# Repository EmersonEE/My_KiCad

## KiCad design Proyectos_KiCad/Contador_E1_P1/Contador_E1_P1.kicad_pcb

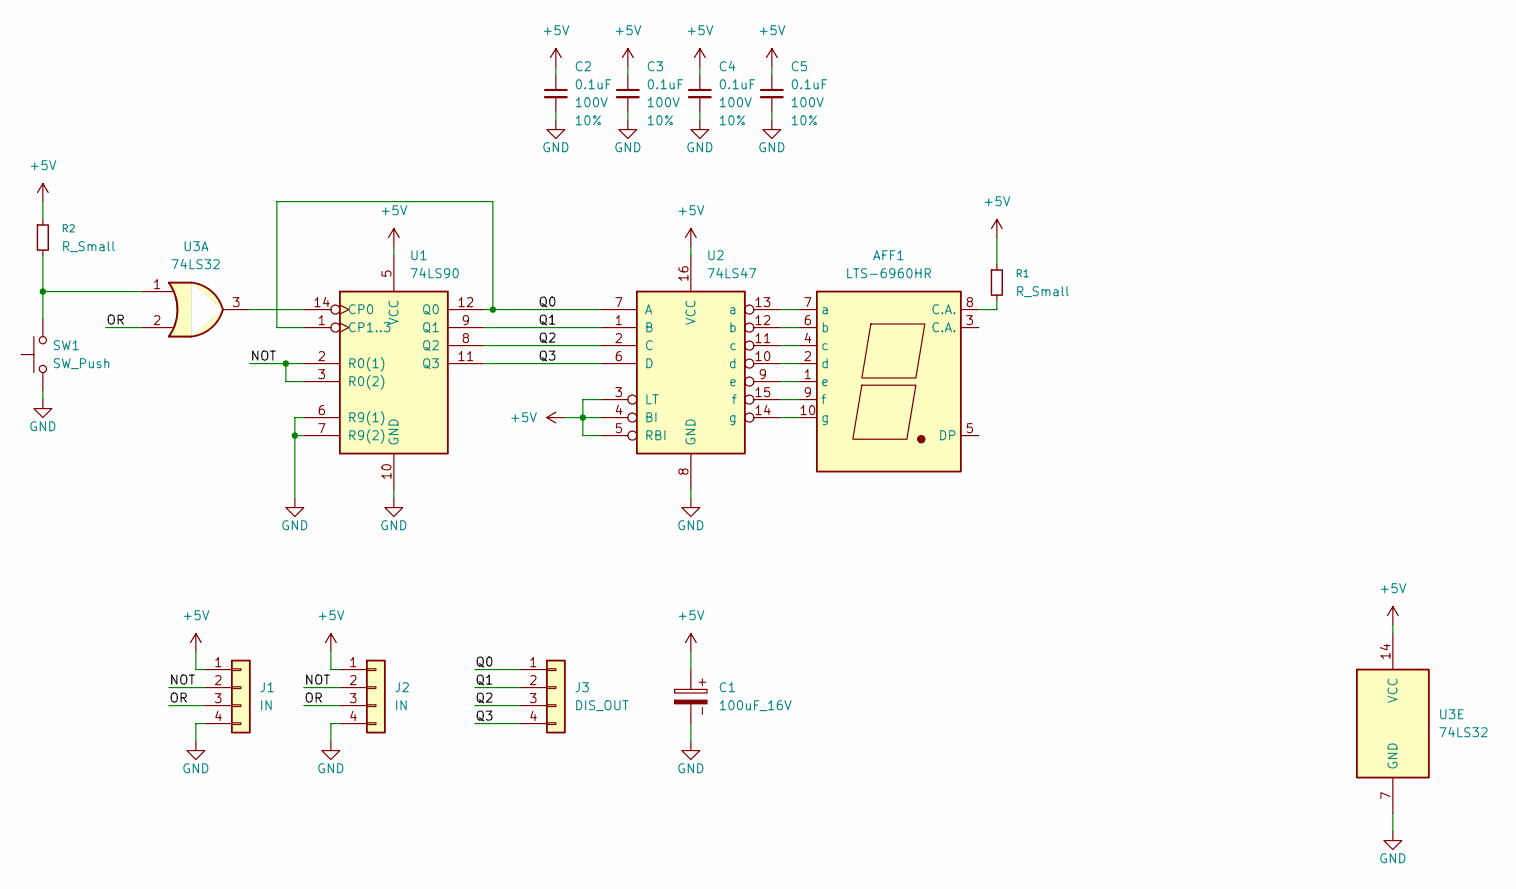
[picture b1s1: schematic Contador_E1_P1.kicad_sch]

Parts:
AFF1: LTS-6960HR; 7SegmentLED_LTS6760_LTS6780
C1: 100uF_16V; CP_Radial_D5.0mm_P2.00mm
C2, C3, C4, C5: 0.1uF; C_0805_2012Metric; Voltage 100V; Tolerance 10%
J1, J2: IN; PinHeader_1x04_P2.54mm_Vertical
J3: DIS_OUT; PinHeader_1x04_P2.54mm_Vertical
R1, R2: R_Small; 1K
SW1: SW_Push; SW_PUSH_6mm
U1: 74LS90; DIP-14_W7.62mm_LongPads
U2: 74LS47; DIP-16_W7.62mm_LongPads
U3: 74LS32; DIP-14_W7.62mm_LongPads

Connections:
+5V: C1.1, C2.1, C3.1, C4.1, C5.1, J1.1, J2.1, R1.1, R2.1, U1.5 (VCC), U2.3 (LT), U2.4 (BI), U2.5 (RBI), U2.16 (VCC), U3.14 (VCC)
/NOT: J1.2, J2.2, U1.2 (R0(1)), U1.3 (R0(2))
/OR: J1.3, J2.3, U3.2
/Q0: J3.1, U1.1 (CP1..3), U1.12 (Q0), U2.7 (A)
/Q1: J3.2, U1.9 (Q1), U2.1 (B)
/Q2: J3.3, U1.8 (Q2), U2.2 (C)
/Q3: J3.4, U1.11 (Q3), U2.6 (D)
GND: C1.2, C2.2, C3.2, C4.2, C5.2, J1.4, J2.4, SW1.1, U1.6 (R9(1)), U1.7 (R9(2)), U1.10 (GND), U2.8 (GND), U3.7 (GND)
unnamed: AFF1.8 (C.A.), R1.2
unnamed: AFF1.7 (a), U2.13 (a)
unnamed: AFF1.6 (b), U2.12 (b)
unnamed: AFF1.4 (c), U2.11 (c)
unnamed: AFF1.2 (d), U2.10 (d)
unnamed: AFF1.1 (e), U2.9 (e)
unnamed: AFF1.9 (f), U2.15 (f)
unnamed: AFF1.10 (g), U2.14 (g)
unnamed: R2.2, SW1.2, U3.1
unnamed: U1.14 (CP0), U3.3

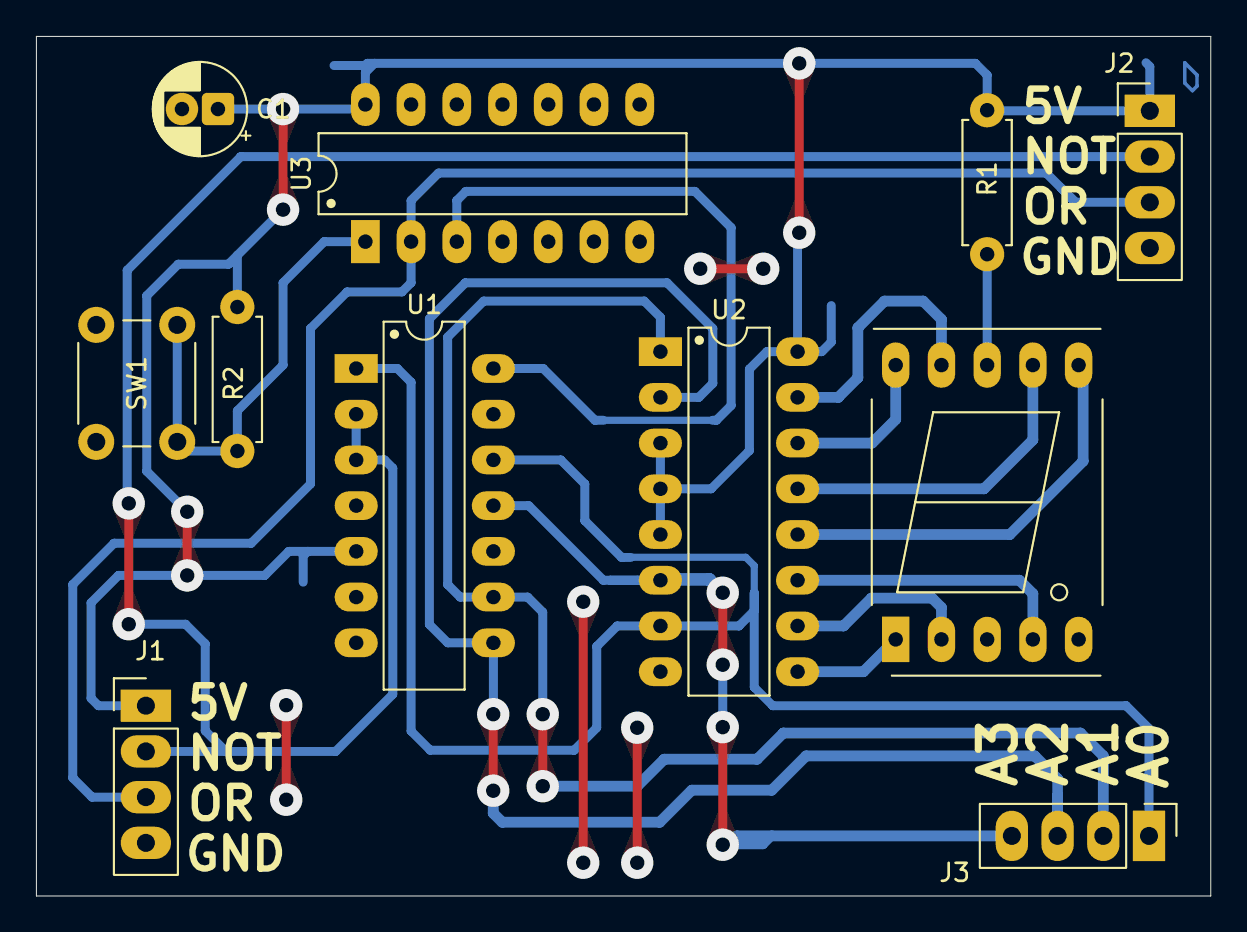
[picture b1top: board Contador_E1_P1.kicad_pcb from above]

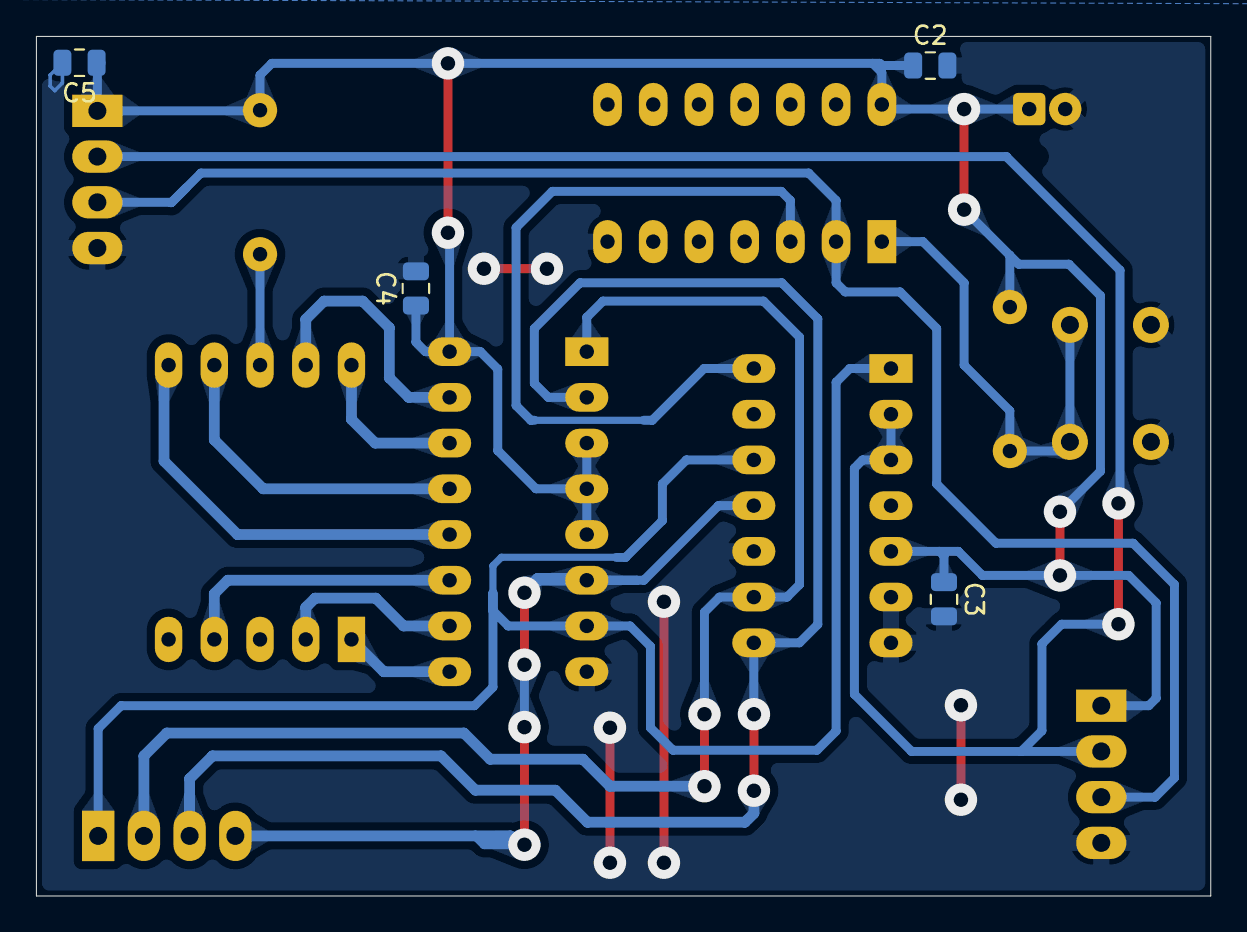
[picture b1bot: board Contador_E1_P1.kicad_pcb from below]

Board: 2 copper layers, 65.2 x 47.8 mm, 15 parts (4 on the bottom side), 18 nets.

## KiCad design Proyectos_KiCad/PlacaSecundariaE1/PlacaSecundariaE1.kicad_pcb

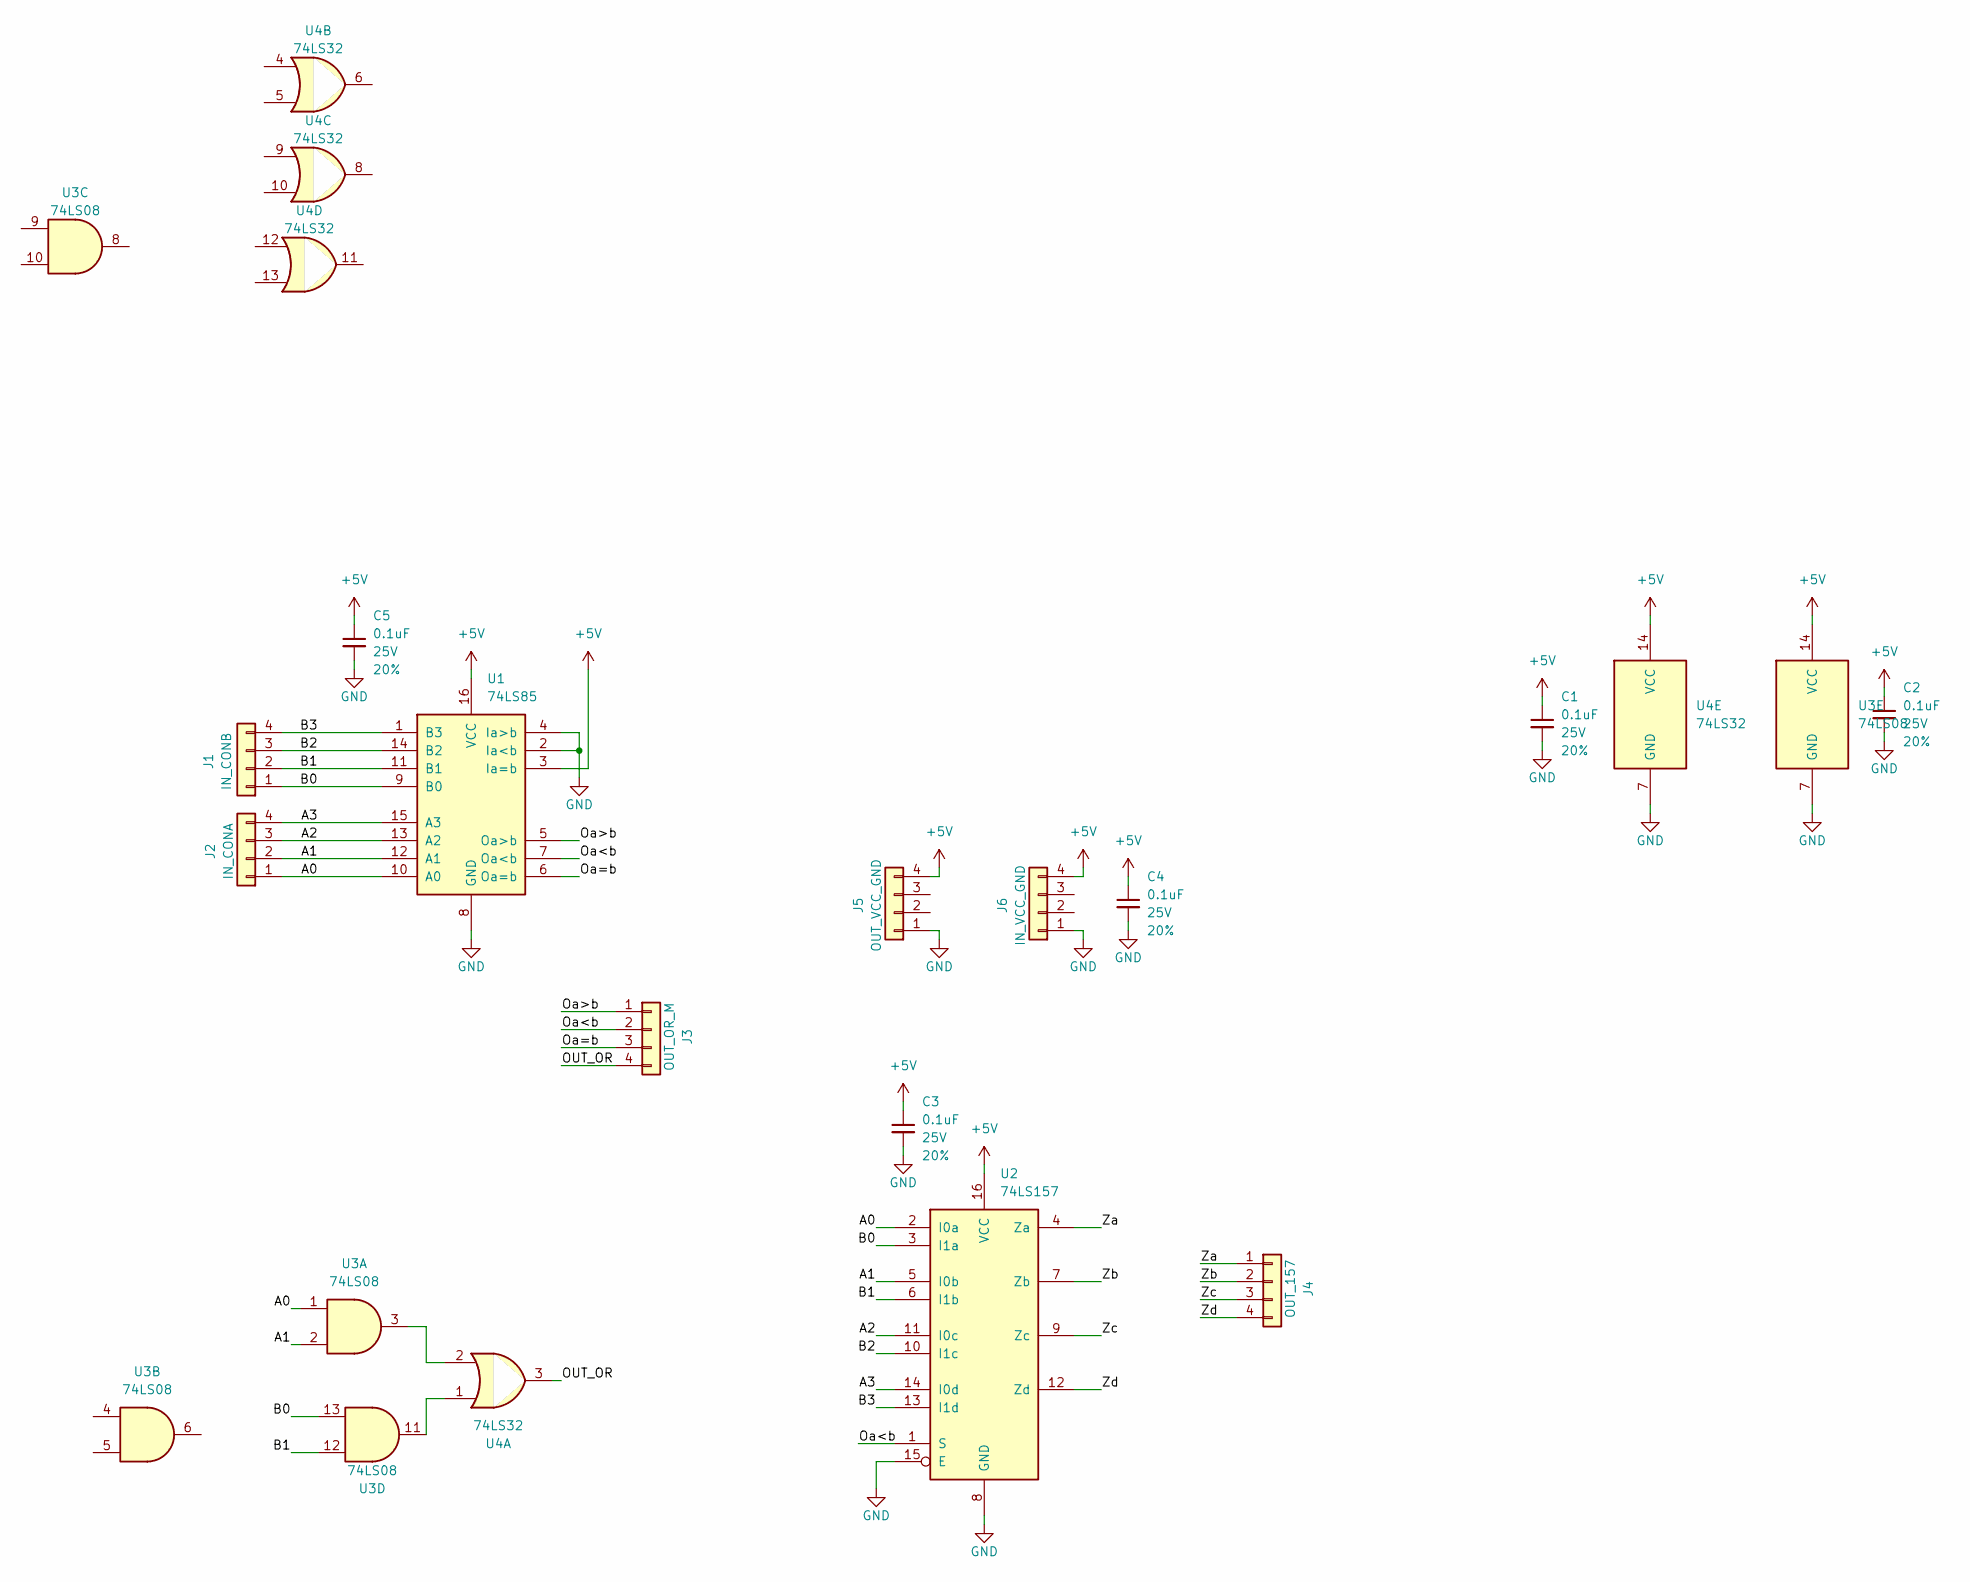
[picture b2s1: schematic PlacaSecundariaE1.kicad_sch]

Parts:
C1, C2, C3, C4, C5: 0.1uF; C_0805_2012Metric; Voltage 25V; Tolerance 20%
J1: IN_CONB; PinHeader_1x04_P2.54mm_Vertical
J2: IN_CONA; PinHeader_1x04_P2.54mm_Vertical
J3: OUT_OR_M; PinHeader_1x04_P2.54mm_Vertical
J4: OUT_157; PinHeader_1x04_P2.54mm_Vertical
J5: OUT_VCC_GND; PinHeader_1x04_P2.54mm_Vertical
J6: IN_VCC_GND; PinHeader_1x04_P2.54mm_Vertical
U1: 74LS85; DIP-16_W7.62mm_LongPads
U2: 74LS157; DIP-16_W7.62mm_LongPads
U3: 74LS08; DIP-14_W7.62mm_LongPads
U4: 74LS32; DIP-14_W7.62mm_LongPads

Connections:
+5V: C1.1, C2.1, C3.1, C4.1, C5.1, J5.4, J6.4, U1.3 (Ia=b), U1.16 (VCC), U2.16 (VCC), U3.14 (VCC), U4.14 (VCC)
/A0: J2.1, U1.10 (A0), U2.2 (I0a), U3.1
/A1: J2.2, U1.12 (A1), U2.5 (I0b), U3.2
/A2: J2.3, U1.13 (A2), U2.11 (I0c)
/A3: J2.4, U1.15 (A3), U2.14 (I0d)
/B0: J1.1, U1.9 (B0), U2.3 (I1a), U3.13
/B1: J1.2, U1.11 (B1), U2.6 (I1b), U3.12
/B2: J1.3, U1.14 (B2), U2.10 (I1c)
/B3: J1.4, U1.1 (B3), U2.13 (I1d)
/OUT_OR: J3.4, U4.3
/Oa<b: J3.2, U1.7 (Oa<b), U2.1 (S)
/Oa=b: J3.3, U1.6 (Oa=b)
/Oa>b: J3.1, U1.5 (Oa>b)
/Za: J4.1, U2.4 (Za)
/Zb: J4.2, U2.7 (Zb)
/Zc: J4.3, U2.9 (Zc)
/Zd: J4.4, U2.12 (Zd)
GND: C1.2, C2.2, C3.2, C4.2, C5.2, J5.1, J6.1, U1.2 (Ia<b), U1.4 (Ia>b), U1.8 (GND), U2.8 (GND), U2.15 (E), U3.7 (GND), U4.7 (GND)
unnamed: U3.3, U4.2
unnamed: U3.11, U4.1

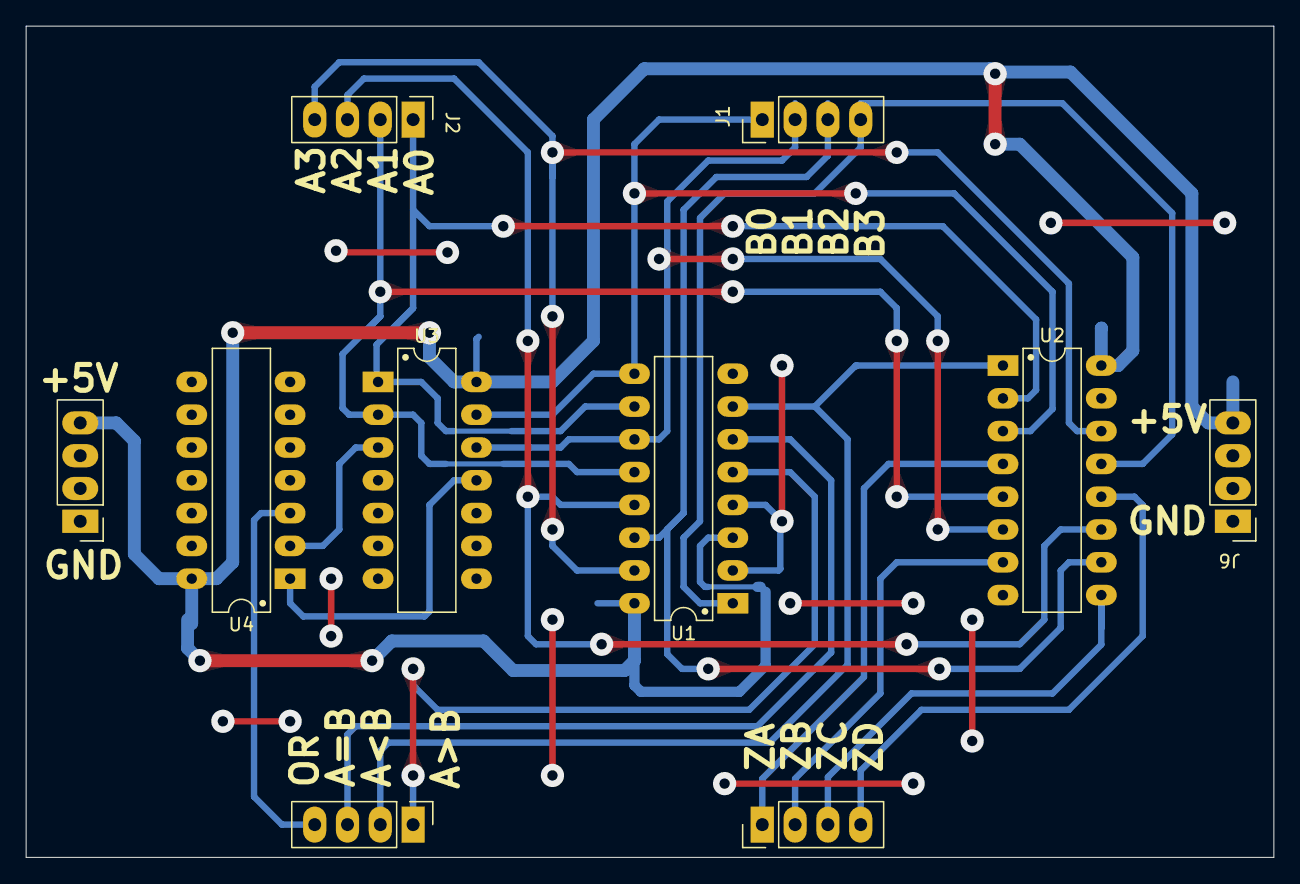
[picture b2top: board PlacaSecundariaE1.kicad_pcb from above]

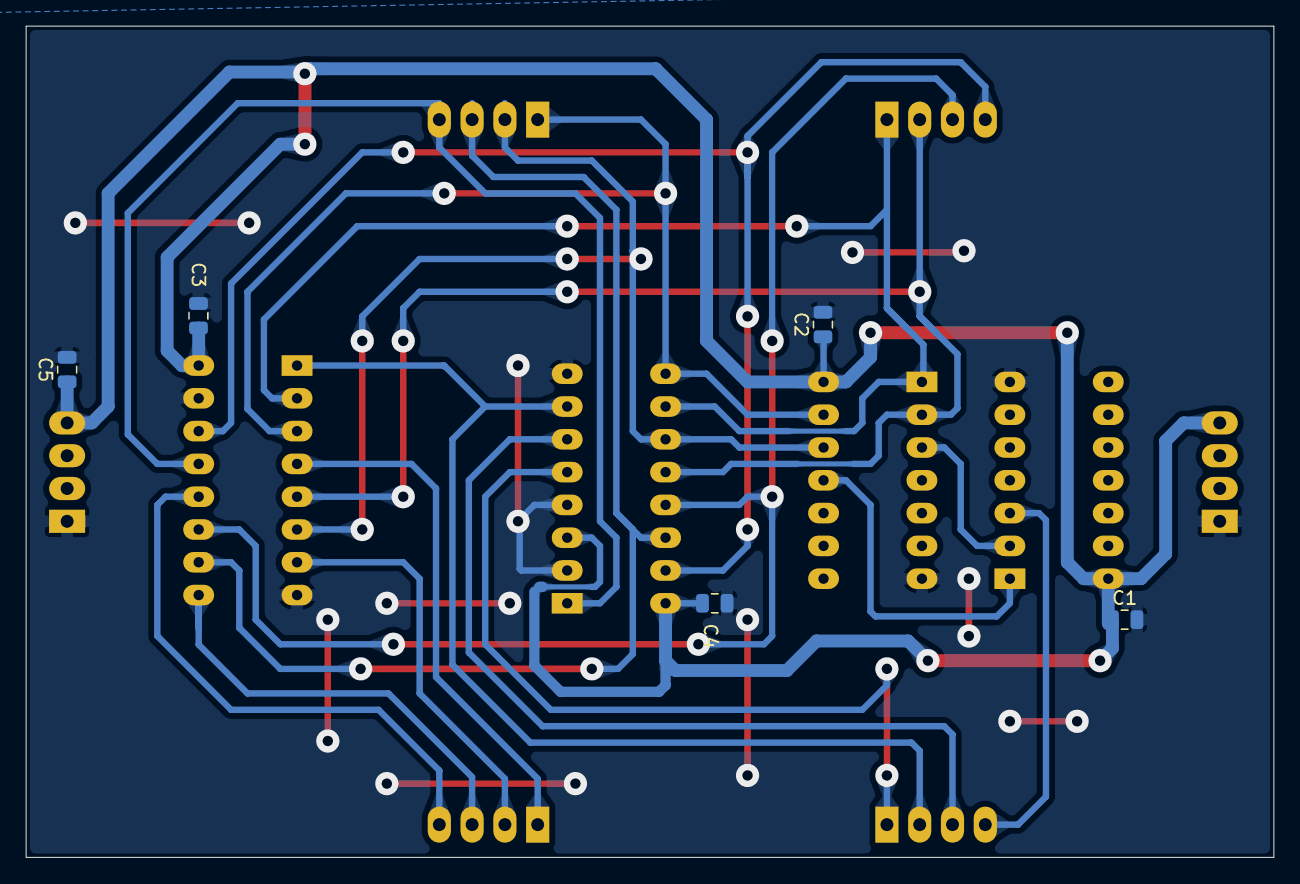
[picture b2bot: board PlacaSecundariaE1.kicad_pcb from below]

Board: 2 copper layers, 96.6 x 64.4 mm, 15 parts (5 on the bottom side), 20 nets.

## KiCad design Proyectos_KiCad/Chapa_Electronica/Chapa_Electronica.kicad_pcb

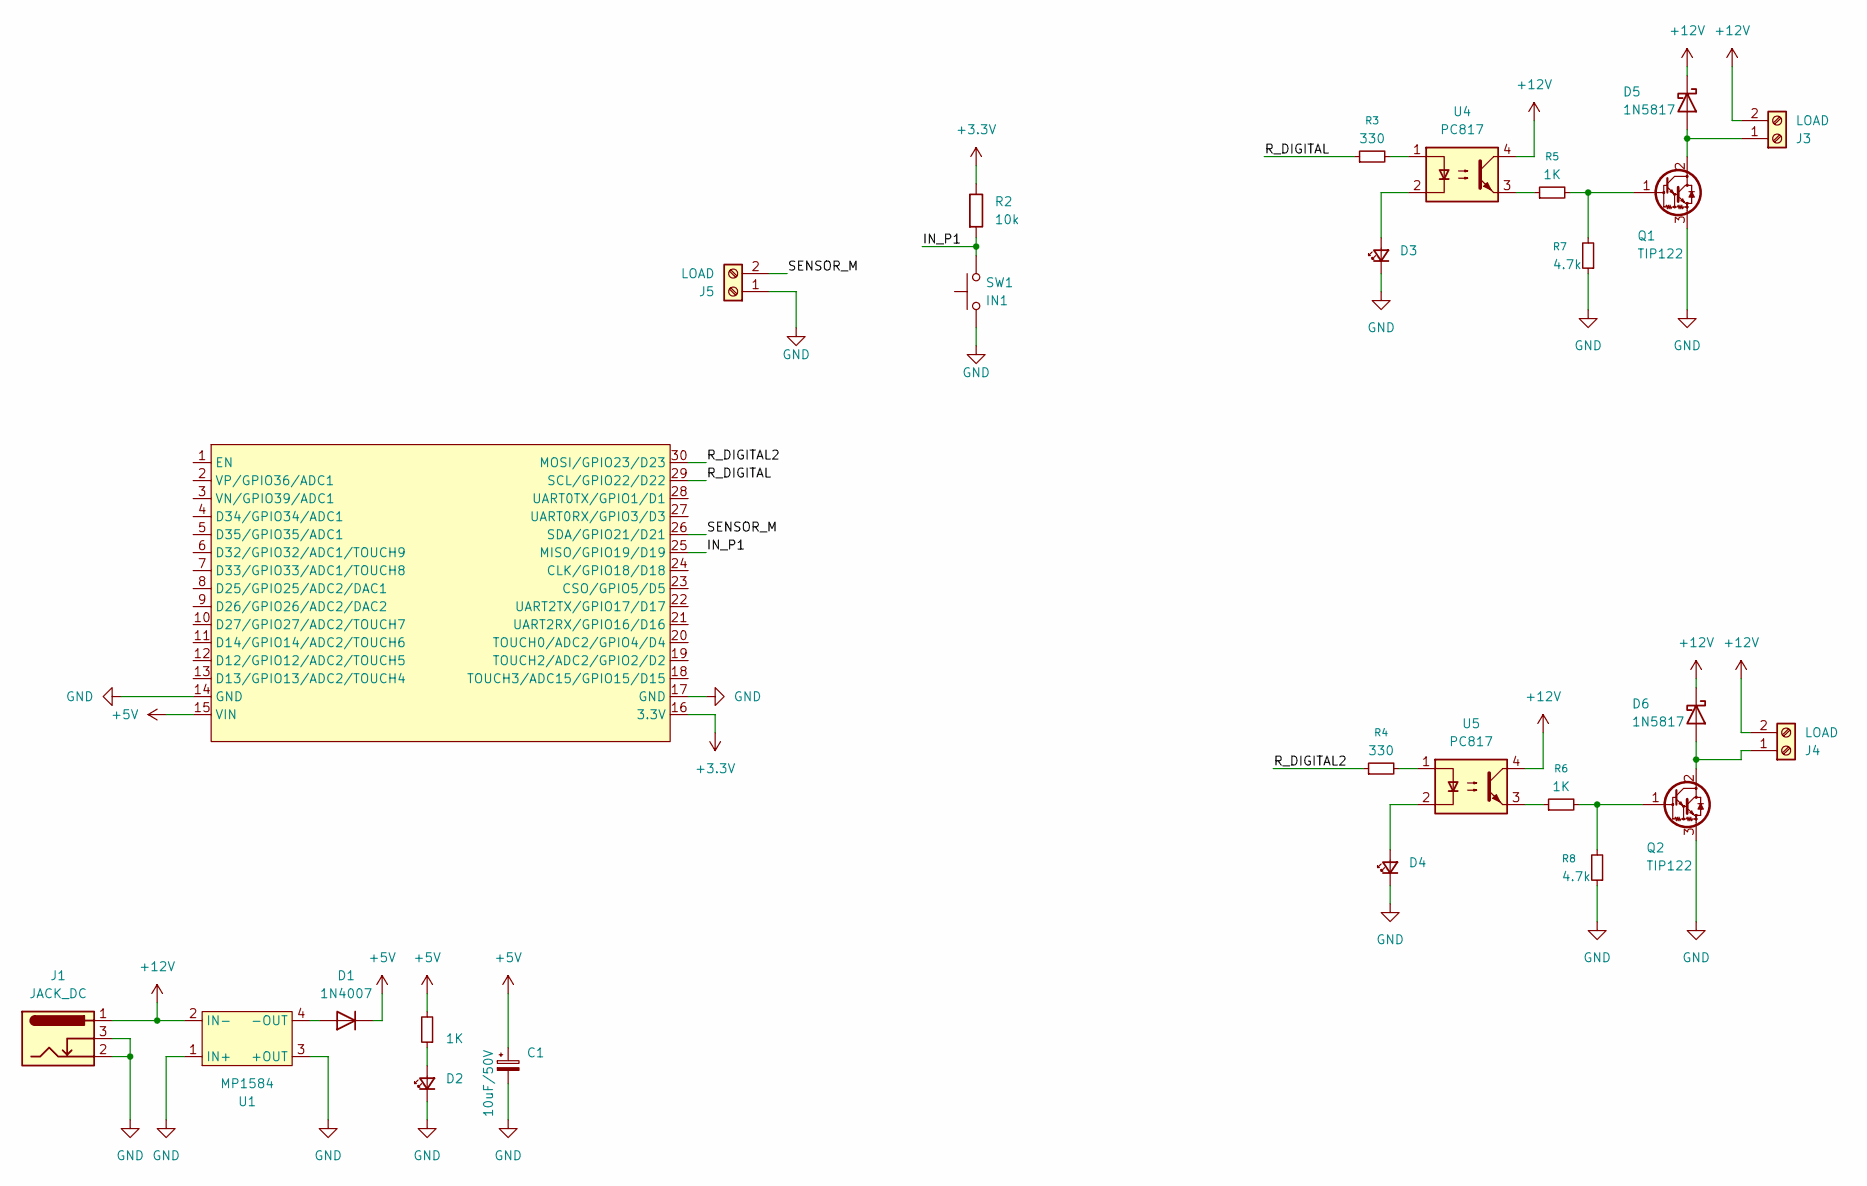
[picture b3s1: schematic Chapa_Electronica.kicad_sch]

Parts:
C1: 10uF/50V; CP_Radial_D4.0mm_P2.00mm
D1: 1N4007; D_DO-41_SOD81_P10.16mm_Horizontal
D2, D3, D4: LED_D5.0mm
D5, D6: 1N5817; D_DO-41_SOD81_P10.16mm_Horizontal
J1: JACK_DC; BarrelJack_GCT_DCJ200-10-A_Horizontal
J3, J4, J5: LOAD; TerminalBlock_Phoenix_MKDS-1,5-2-5.08_1x02_P5.08mm_Horizont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
Q1, Q2: TIP122; TO-220-3_VDC
R1: 1K; 470
R2: 10k; 10K
R3, R4: 330
R5, R6: 1K
R7, R8: 4.7k; 10K
SW1: IN1; Molex_KK-254_AE-6410-02A_1x02_P2.54mm_Vertical; Mfg Part# 8-004 SMD Button 8x3.6mm Height=2.5mm
U1: MP1584; MP1584_Module
U2: ESP32_DevKit_V1_DOIT; ESP32_DEVKIT_V1_E32
U4, U5: PC817; DIP-4_W7.62mm

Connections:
+3.3V: R2.2, U2.16 (3.3V)
+5V: C1.1, D1.1 (K), R1.2, U2.15 (VIN)
+12V: D5.1 (K), D6.1 (K), J1.1, J3.2, J4.2, U1.2 (IN-), U4.4, U5.4
/IN_P1: R2.1, SW1.2, U2.25 (MISO/GPIO19/D19)
/R_DIGITAL: R3.1, U2.29 (SCL/GPIO22/D22)
/R_DIGITAL2: R4.1, U2.30 (MOSI/GPIO23/D23)
/SENSOR_M: J5.2, U2.26 (SDA/GPIO21/D21)
GND: C1.2, D2.1 (K), D3.1 (K), D4.1 (K), J1.2, J1.3, J5.1, Q1.3 (E), Q2.3 (E), R7.1, R8.1, SW1.1, U1.1 (IN+), U1.3 (+OUT), U2.14 (GND), U2.17 (GND)
unnamed: D1.2 (A), U1.4 (-OUT)
unnamed: D2.2 (A), R1.1
unnamed: D3.2 (A), U4.2
unnamed: D4.2 (A), U5.2
unnamed: D5.2 (A), J3.1, Q1.2 (C)
unnamed: D6.2 (A), J4.1, Q2.2 (C)
unnamed: Q1.1 (B), R5.2, R7.2
unnamed: Q2.1 (B), R6.2, R8.2
unnamed: R3.2, U4.1
unnamed: R4.2, U5.1
unnamed: R5.1, U4.3
unnamed: R6.1, U5.3

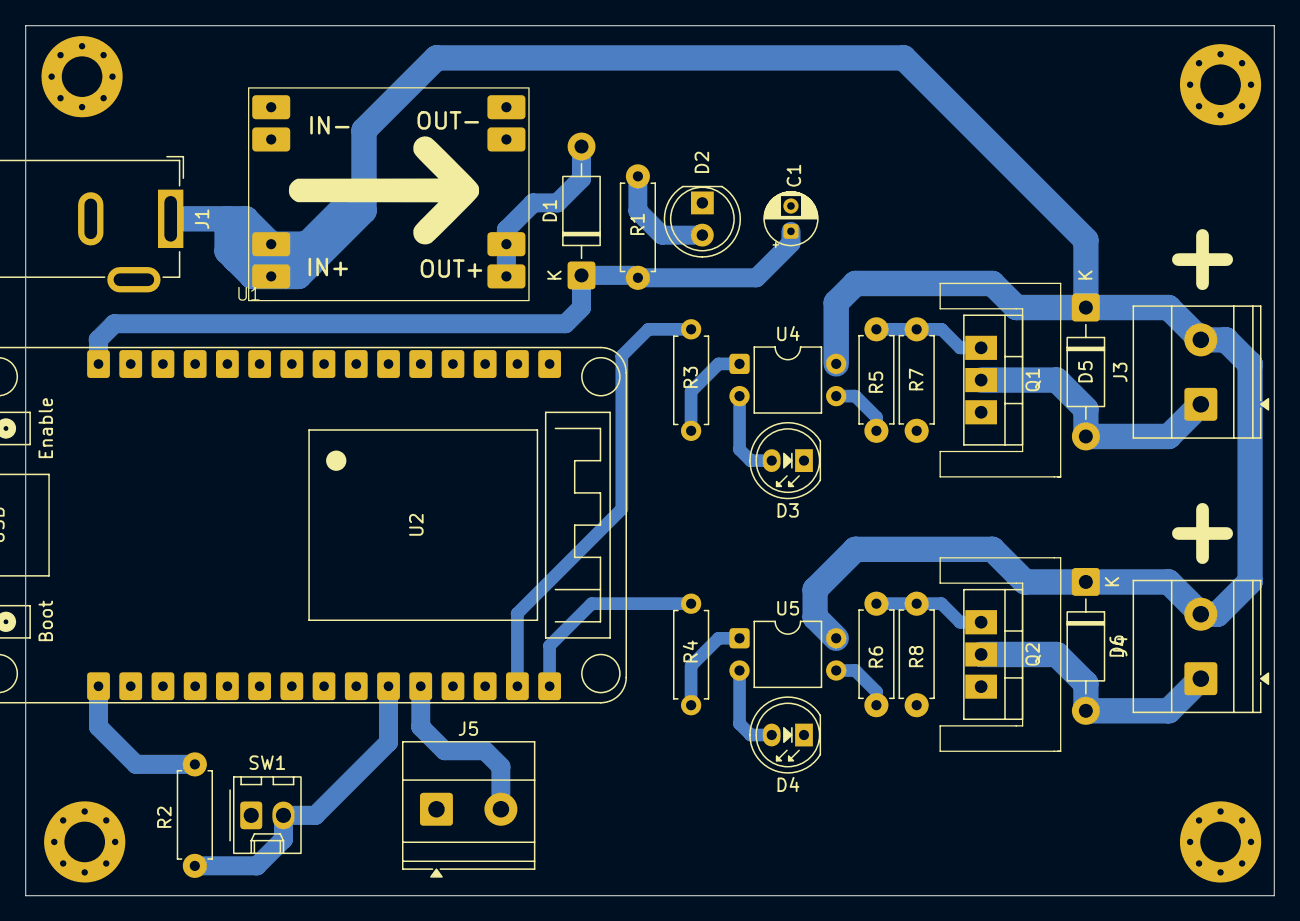
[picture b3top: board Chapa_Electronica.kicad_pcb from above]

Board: 2 copper layers, 98.4 x 68.6 mm, 26 parts (0 on the bottom side), 20 nets.

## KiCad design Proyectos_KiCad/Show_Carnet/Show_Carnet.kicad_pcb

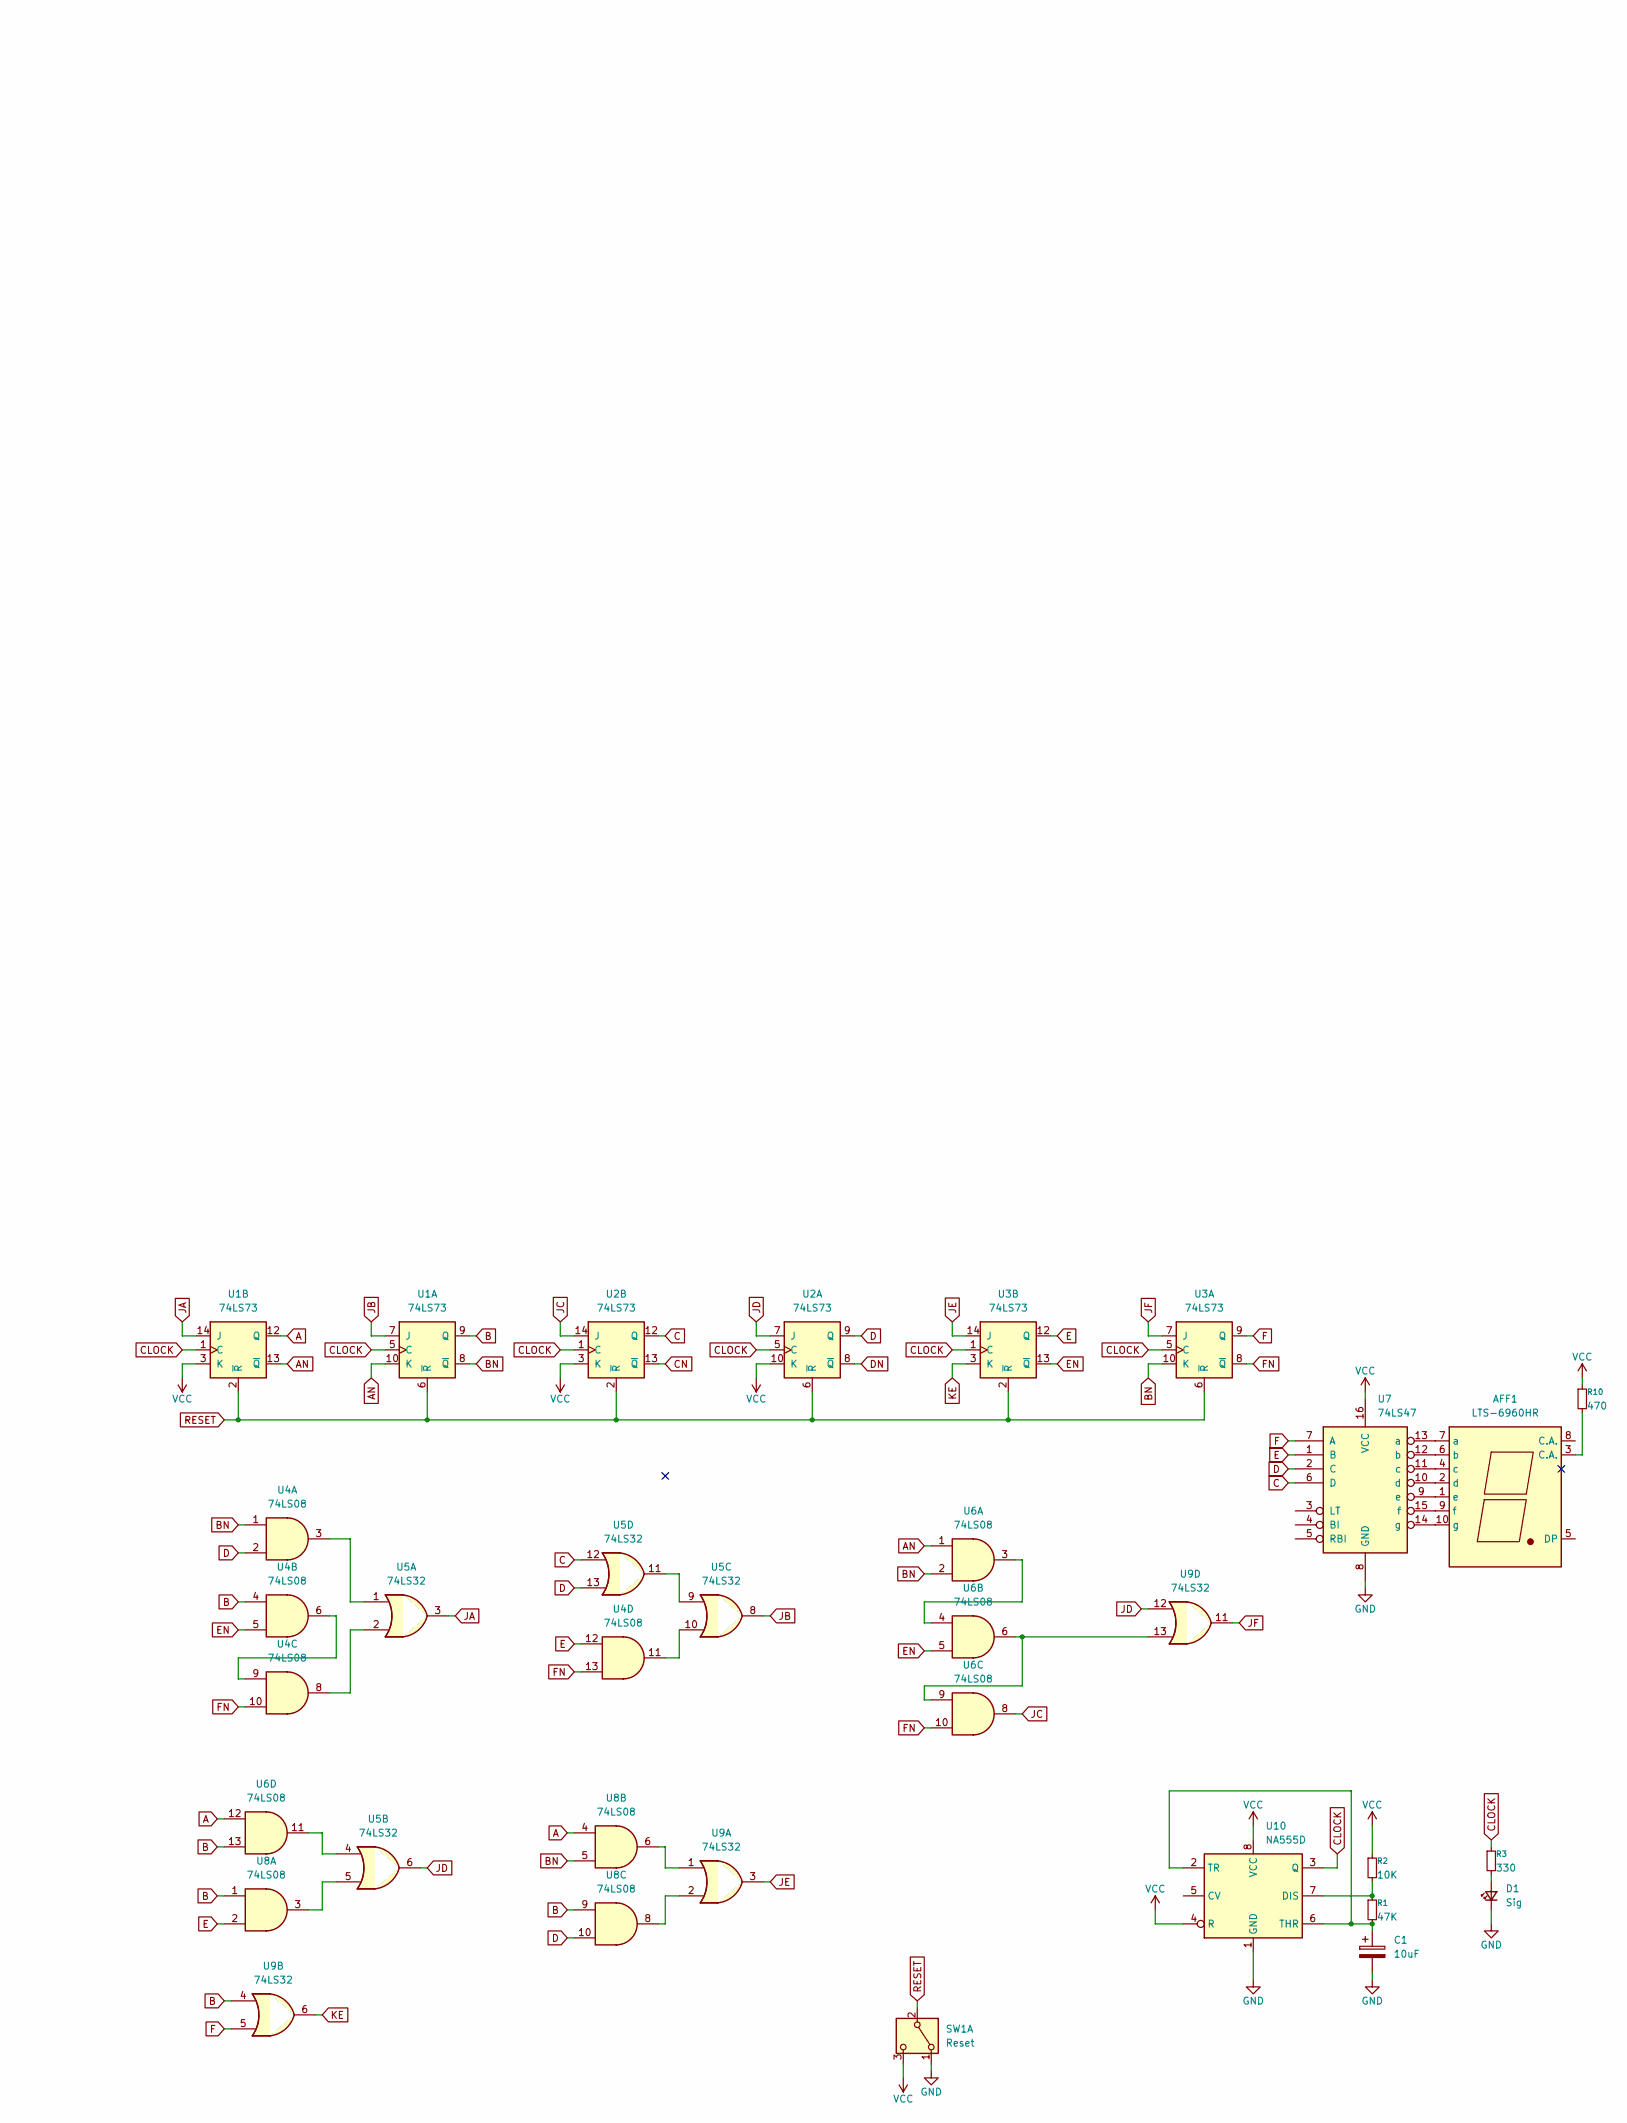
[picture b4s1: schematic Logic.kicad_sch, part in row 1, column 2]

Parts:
AFF1: LTS-6960HR; 7SegmentLED_LTS6760_LTS6780
C1: 10uF; CP_Radial_D5.0mm_P2.50mm
D1: Sig; LED_D5.0mm
R1: 47K; 470
R2: 10K; 470
R3: 330; 470
R10: 470
SW1: Reset; PinHeader_1x03_P2.54mm_Vertical
U1, U2, U3: 74LS73; DIP-14_W7.62mm_LongPads
U4, U6, U8: 74LS08; DIP-14_W7.62mm_LongPads
U5, U9: 74LS32; DIP-14_W7.62mm_LongPads
U7: 74LS47; DIP-16_W7.62mm_LongPads
U10: NA555D; DIP-8_W7.62mm_LongPads

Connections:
A: U1.12 (Q), U6.12, U8.4
AN: U1.10 (K), U1.13 (~Q), U6.1
B: U1.9 (Q), U4.4, U6.13, U8.1, U8.9, U9.4
BN: U1.8 (~Q), U3.10 (K), U4.1, U6.2, U8.5
C: U2.12 (Q), U5.12, U7.6 (D)
CLOCK: R3.1, U1.1 (C), U1.5 (C), U2.1 (C), U2.5 (C), U3.1 (C), U3.5 (C), U10.3 (Q)
CN: U2.13 (~Q)
D: U2.9 (Q), U4.2, U5.13, U7.2 (C), U8.10
DN: U2.8 (~Q)
E: U3.12 (Q), U4.12, U7.1 (B), U8.2
EN: U3.13 (~Q), U4.5, U6.5
F: U3.9 (Q), U7.7 (A), U9.5
FN: U3.8 (~Q), U4.10, U4.13, U6.10
GND: C1.2, D1.1 (K), SW1.1 (A), U7.8 (GND), U10.1 (GND); also elsewhere on the board
JA: U1.14 (J), U5.3
JB: U1.7 (J), U5.8
JC: U2.14 (J), U6.8
JD: U2.7 (J), U5.6, U9.12
JE: U3.14 (J), U9.3
JF: U3.7 (J), U9.11
KE: U3.3 (K), U9.6
unnamed: AFF1.3 (C.A.), R10.2
unnamed: AFF1.7 (a), U7.13 (a)
unnamed: AFF1.6 (b), U7.12 (b)
unnamed: AFF1.4 (c), U7.11 (c)
unnamed: AFF1.2 (d), U7.10 (d)
unnamed: AFF1.1 (e), U7.9 (e)
unnamed: AFF1.9 (f), U7.15 (f)
unnamed: AFF1.10 (g), U7.14 (g)
unnamed: D1.2 (A), R3.2
unnamed: U4.3, U5.1
unnamed: U4.6, U4.9
unnamed: U4.8, U5.2
unnamed: U4.11, U5.10
unnamed: U5.4, U6.11
unnamed: U5.5, U8.3
unnamed: U5.9, U5.11
unnamed: U6.3, U6.4
unnamed: U6.6, U6.9, U9.13
unnamed: U8.6, U9.1
unnamed: U8.8, U9.2
unnamed: R1.1, R2.2, U10.7 (DIS)
unnamed: C1.1, R1.2, U10.2 (TR), U10.6 (THR)
RESET: SW1.2 (B), U1.2 (~R), U1.6 (~R), U2.2 (~R), U2.6 (~R), U3.2 (~R), U3.6 (~R)
VCC: R2.1, R10.1, SW1.3 (C), U1.3 (K), U2.3 (K), U2.10 (K), U7.16 (VCC), U10.4 (R), U10.8 (VCC); also elsewhere on the board

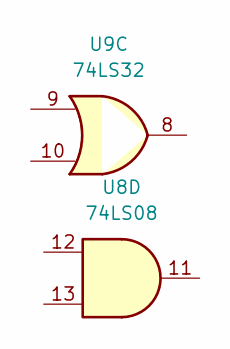
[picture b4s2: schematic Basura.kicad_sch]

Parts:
U8: 74LS08; DIP-14_W7.62mm_LongPads
U9: 74LS32; DIP-14_W7.62mm_LongPads

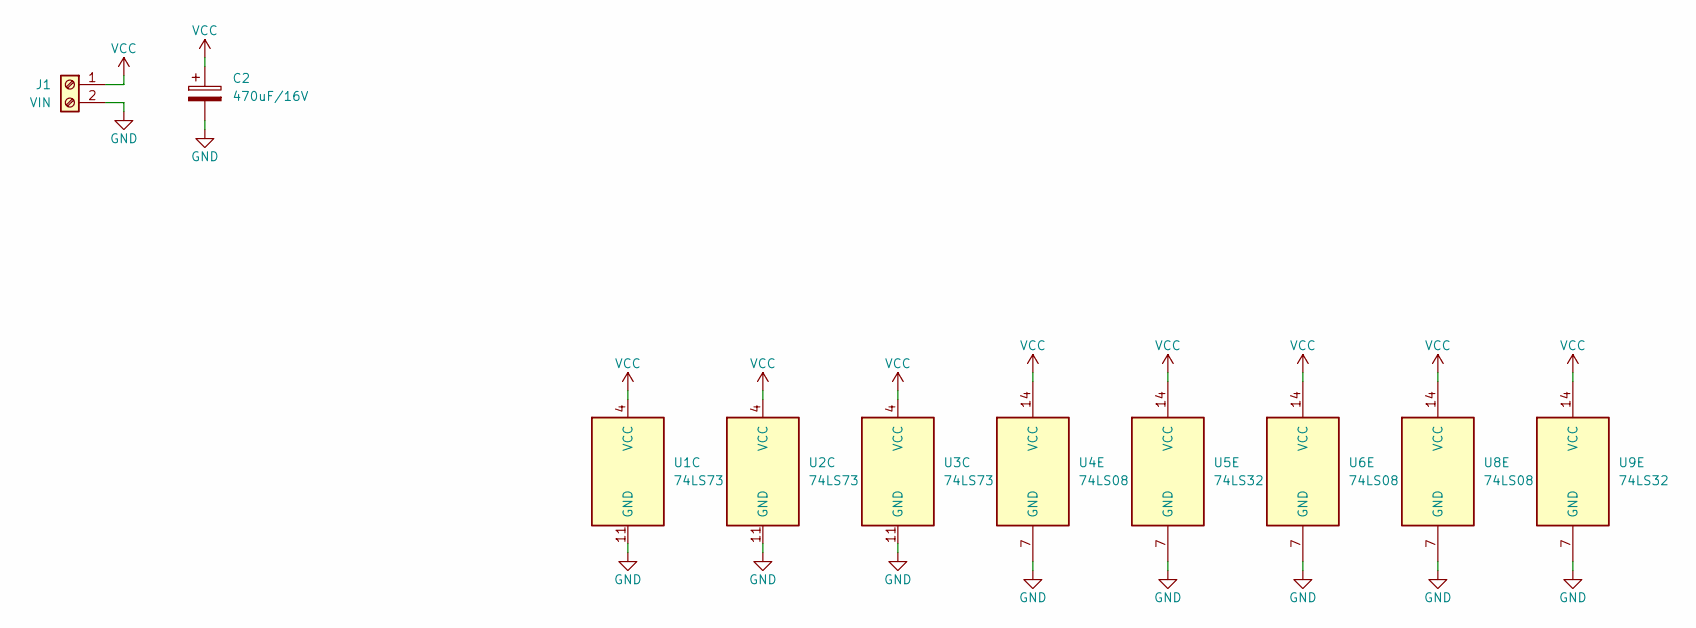
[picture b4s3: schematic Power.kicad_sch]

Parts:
C2: 470uF/16V; CP_Radial_D7.5mm_P2.50mm
J1: VIN; TerminalBlock_Phoenix_MKDS-1,5-2-5.08_1x02_P5.08mm_Horizont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
U1, U2, U3: 74LS73; DIP-14_W7.62mm_LongPads
U4, U6, U8: 74LS08; DIP-14_W7.62mm_LongPads
U5, U9: 74LS32; DIP-14_W7.62mm_LongPads

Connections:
GND: C2.2, J1.2, U1.11 (GND), U2.11 (GND), U3.11 (GND), U4.7 (GND), U5.7 (GND), U6.7 (GND), U8.7 (GND), U9.7 (GND); also elsewhere on the board
VCC: C2.1, J1.1, U1.4 (VCC), U2.4 (VCC), U3.4 (VCC), U4.14 (VCC), U5.14 (VCC), U6.14 (VCC), U8.14 (VCC), U9.14 (VCC); also elsewhere on the board

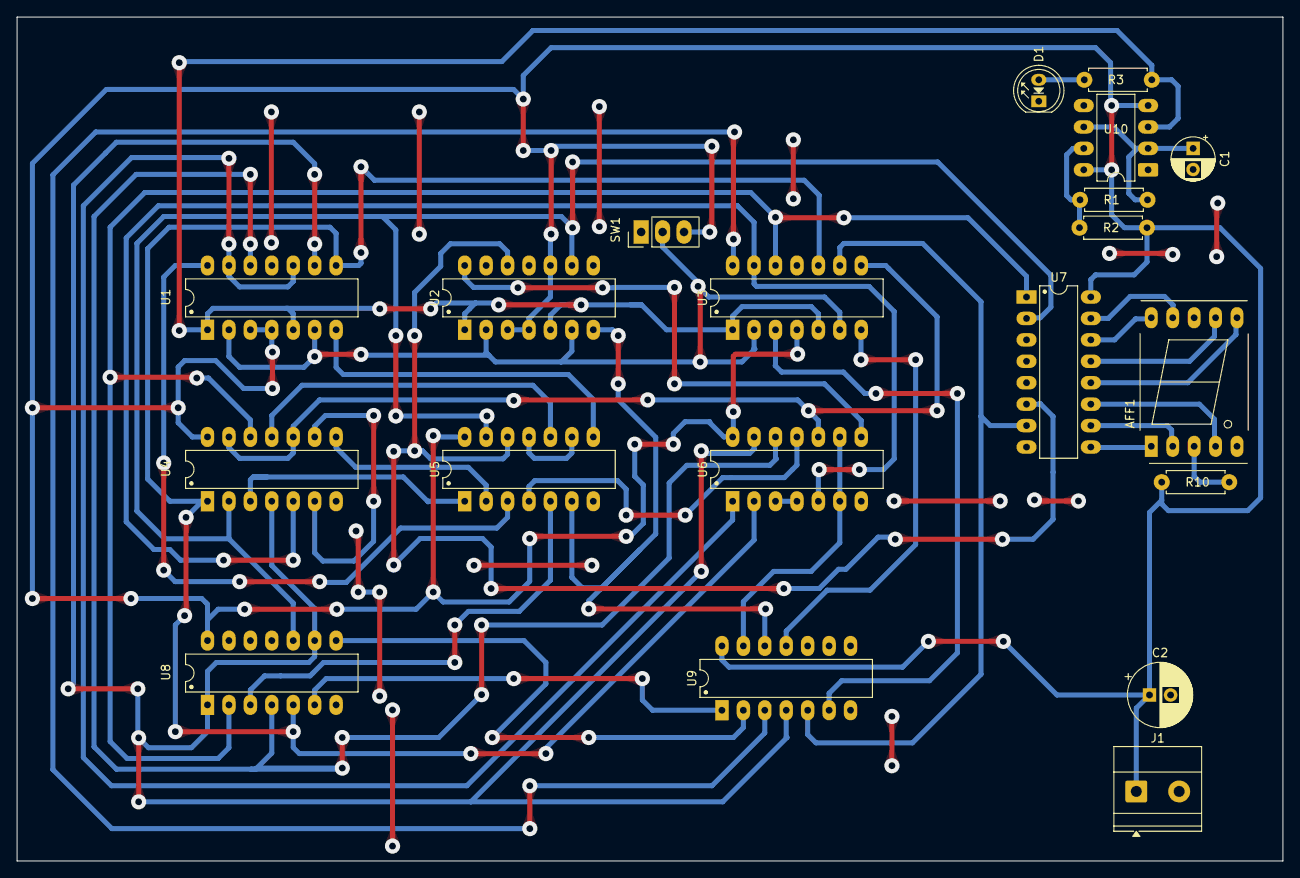
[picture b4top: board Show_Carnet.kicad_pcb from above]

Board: 2 copper layers, 150.0 x 100.0 mm, 20 parts (0 on the bottom side), 43 nets.
